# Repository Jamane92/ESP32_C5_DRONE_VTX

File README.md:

# ESP32_C5_DRONE_VTX

Ce projet à été réalisé individuellement en parallèle de mes études. C'est un module d'émission vidéo en digital à bas coût. Souhaitant me challenger dans mon parcours d'apprentissage en conception hardware, je me suis lancé le défi de construire un drone moi même, avec en première étape de ce gros projet, de faire un VTX ainsi qu'un Flight Controler (FC) de A à Z. Le projet Flight Controler est disponible sur cette page : https://github.com/Jamane92/Flight_Controler_STM32F405RGT6. 

Qu'est ce qu'un module VTX ? C'est un module d'émission vidéo, qui permet de transmettre la vue à la première personne du drone sur un écran au sol, que ce soit un téléphone ou un ordinateur par exemple. Cela permet de repérer le drone dans l'espace et de le faire voler à des endroits où nous ne pouvons pas voir. Un set complet bas/milieu de gamme coùute aux alentours de 200 à 250€. Ca fait mal. J'ai donc décidé, pour m'apprendre à implémenter une chip ESP32 sur PCB, de faire un PCB custom qui intègre une ESP32-C5-WROOM-1U-N8R8, une OV5640 ainsi qu'une carte SD, pour la somme ≈ 40€. Ce qui est un prix imbattable, tout simplement.

Le but de se projet est simple : d'un point de vue technique, m'apprendre à router des SoC (System On Chip) ainsi que des signaux critiques comme ceux de la caméra OV5640, le tout sur mon premier PCB 4 couches avec des composants SMD. Un grand pas donc depuis mon premier PCB sur mon robot équilibriste (https://github.com/Jamane92/Self_Balancing_Robot). Plus de détail dans les rubriques sur les choix de design (notamment sur des améliorations possibles).

Voilà à quoi ressemble le module : 

Plus en détail, le coeur au milieu, à gauche l'antenne Lollipop et à droite la caméra. Ce PCB à fonctionné du premier coup. Voici à quoi ressemble l'interface WEB : 

Voici un petit exemple de ce dont il est capable (entre autres : réglage de a qualité vidéo, compression, luminosité, saturation, contraste, filtre, enregistrement sur la SD Card) :

Voici une vidéo de mon balcon, au 3ème étage, avec l'exploration de tous les settings de la caméra : 

Voici une vidéo de moi en HVGA (480 × 320), gardez à l'esprit que l'on filmera en SVGA (800 × 600), soit littéralement 3 fois plus de pixels. 

Pour la démo en vol, il faudra attendre que le projet du flight controler (https://github.com/Jamane92/Flight_Controler_STM32F405RGT6) soit terminé. 

Pour voir les performances du montage, voir le folder dedié.

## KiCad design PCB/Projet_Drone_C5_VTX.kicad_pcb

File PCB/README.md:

Ce PCB contient **4 couches**, étant embarqué sur un drone, il possède des entrées d'alimentations **+5V**, que sont l'**USB-C**, également utilisé pour programmer l'**ESP32**, ainsi que des PADs de cuivre, qui viendront directement être branché à partir de mon flight controler. Il possède deux diodes Schottky pour faire du **OR'ing**. Une **OV5640**, un lecteur de **carte SD**, ainsi qu'un **module 1U** spécialement choisi pour la possibilité d'y brancher une **antenne**, qui est une **lollipop** en RHCP, mieux qu'une antenne "simple", car celle-ci émettra un signal en forme de cercle, parfaitement adapté pour une antenne en hauteur qui va communiquer avec le sol.

Je suis parti sur un **4 couches** pour me simplifier la vie. Mon stack-up est le suivant : 

  - L1 : SIGNAL
  - L2 : GND
  - L3 : GND
  - L4 : SIGNAL/POWER

Tous les composants sont sur la même face pour des raisons économiques (plus cher de faire les deux face lors de l'assemblage chez JLCPCB). 

Afin d'optimiser l'**intégrité des signaux**, de nombreux vias de masse (ground vias) ont été placés pour relier **(stitching)** les plans de masse entre les couches L2 et L3. Ce **stitching de masse assure un chemin de retour court**, direct et ininterrompu pour les signaux numériques à haute vitesse (bus de la caméra OV5640, interface de la carte SD) ainsi que pour la section RF à 5.8 GHz. Cela permet de **minimiser l'inductance des boucles de courant** et de **réduire drastiquement les interférences électromagnétiques** (EMI), un point absolument **critique** dans l'environnement très bruyant d'un drone (ESC, moteurs). 

L'**impédance** de la ligne de communication différentiel D+/D- est **matché à 90Ω**

Voici la schématique : 

Voici le routage : 

Voici la 3D :

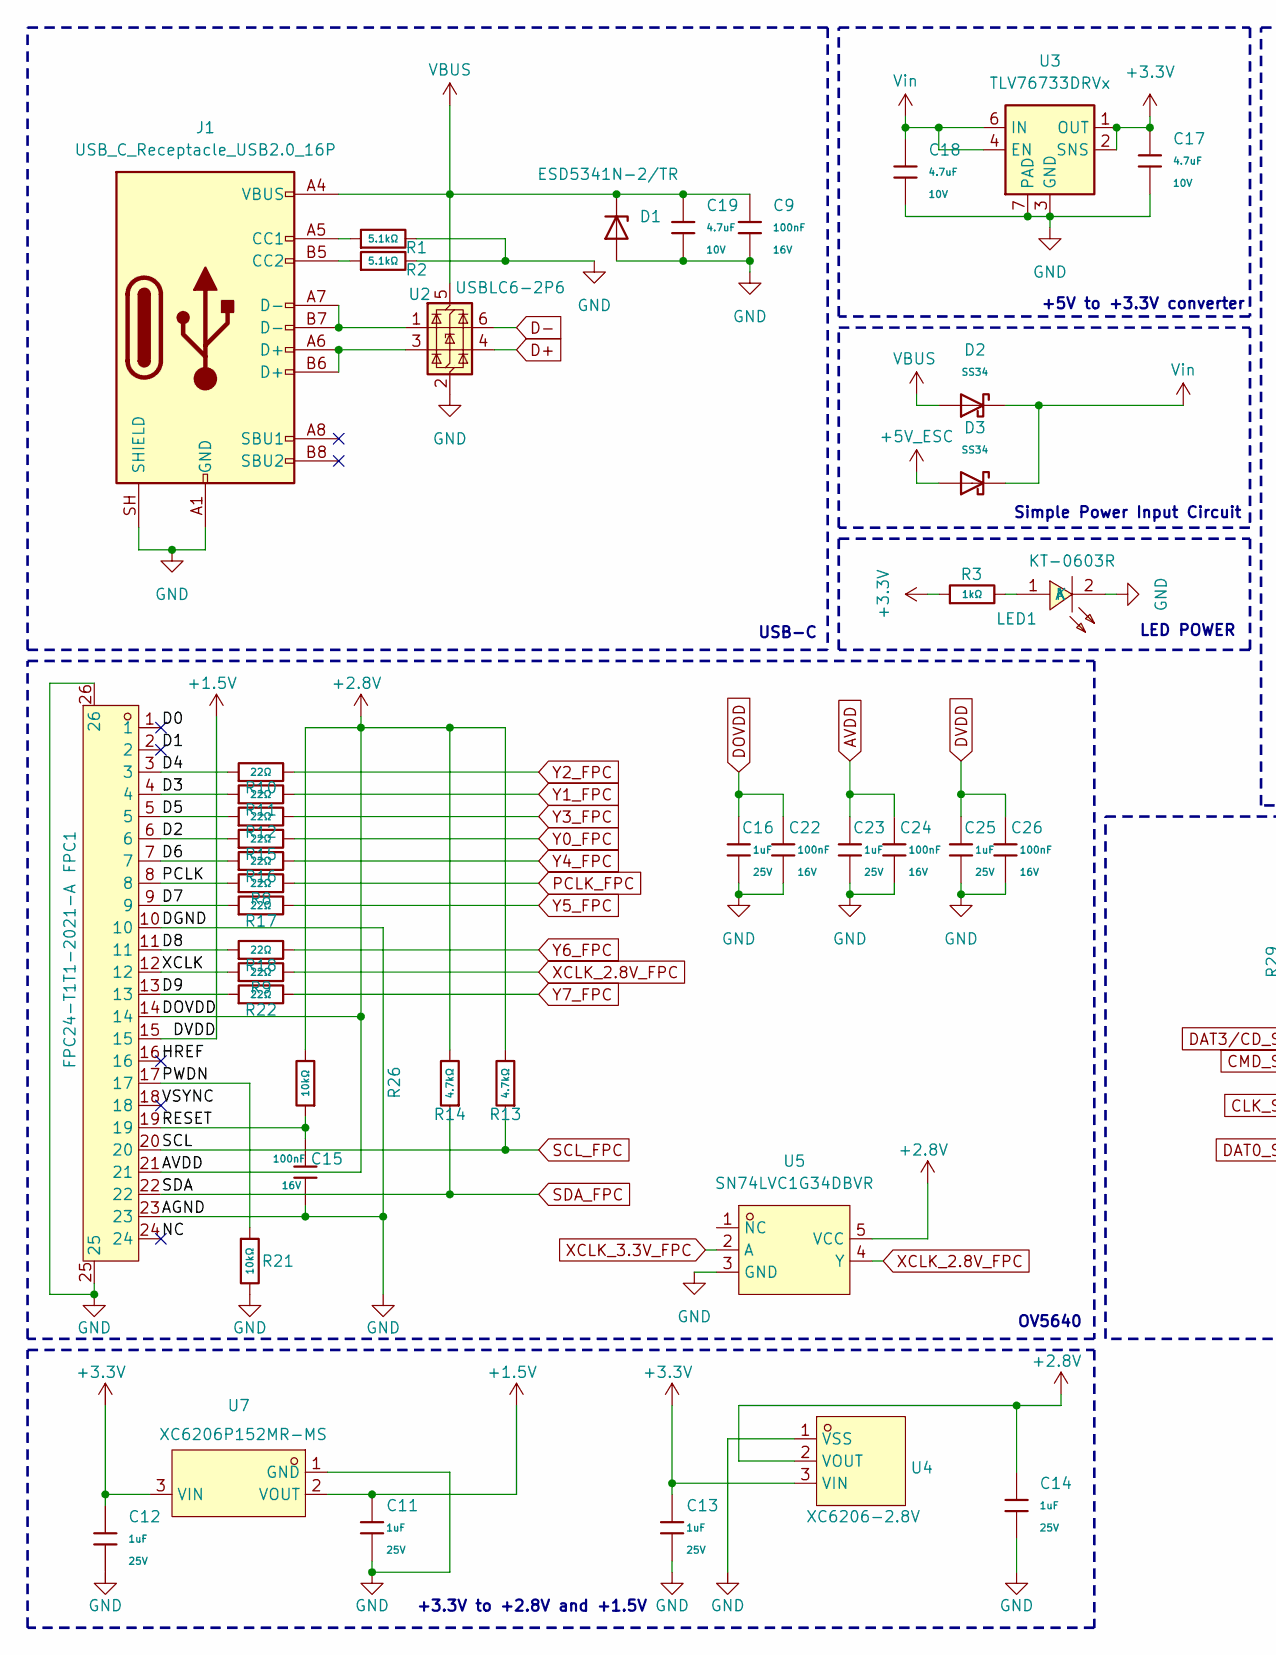
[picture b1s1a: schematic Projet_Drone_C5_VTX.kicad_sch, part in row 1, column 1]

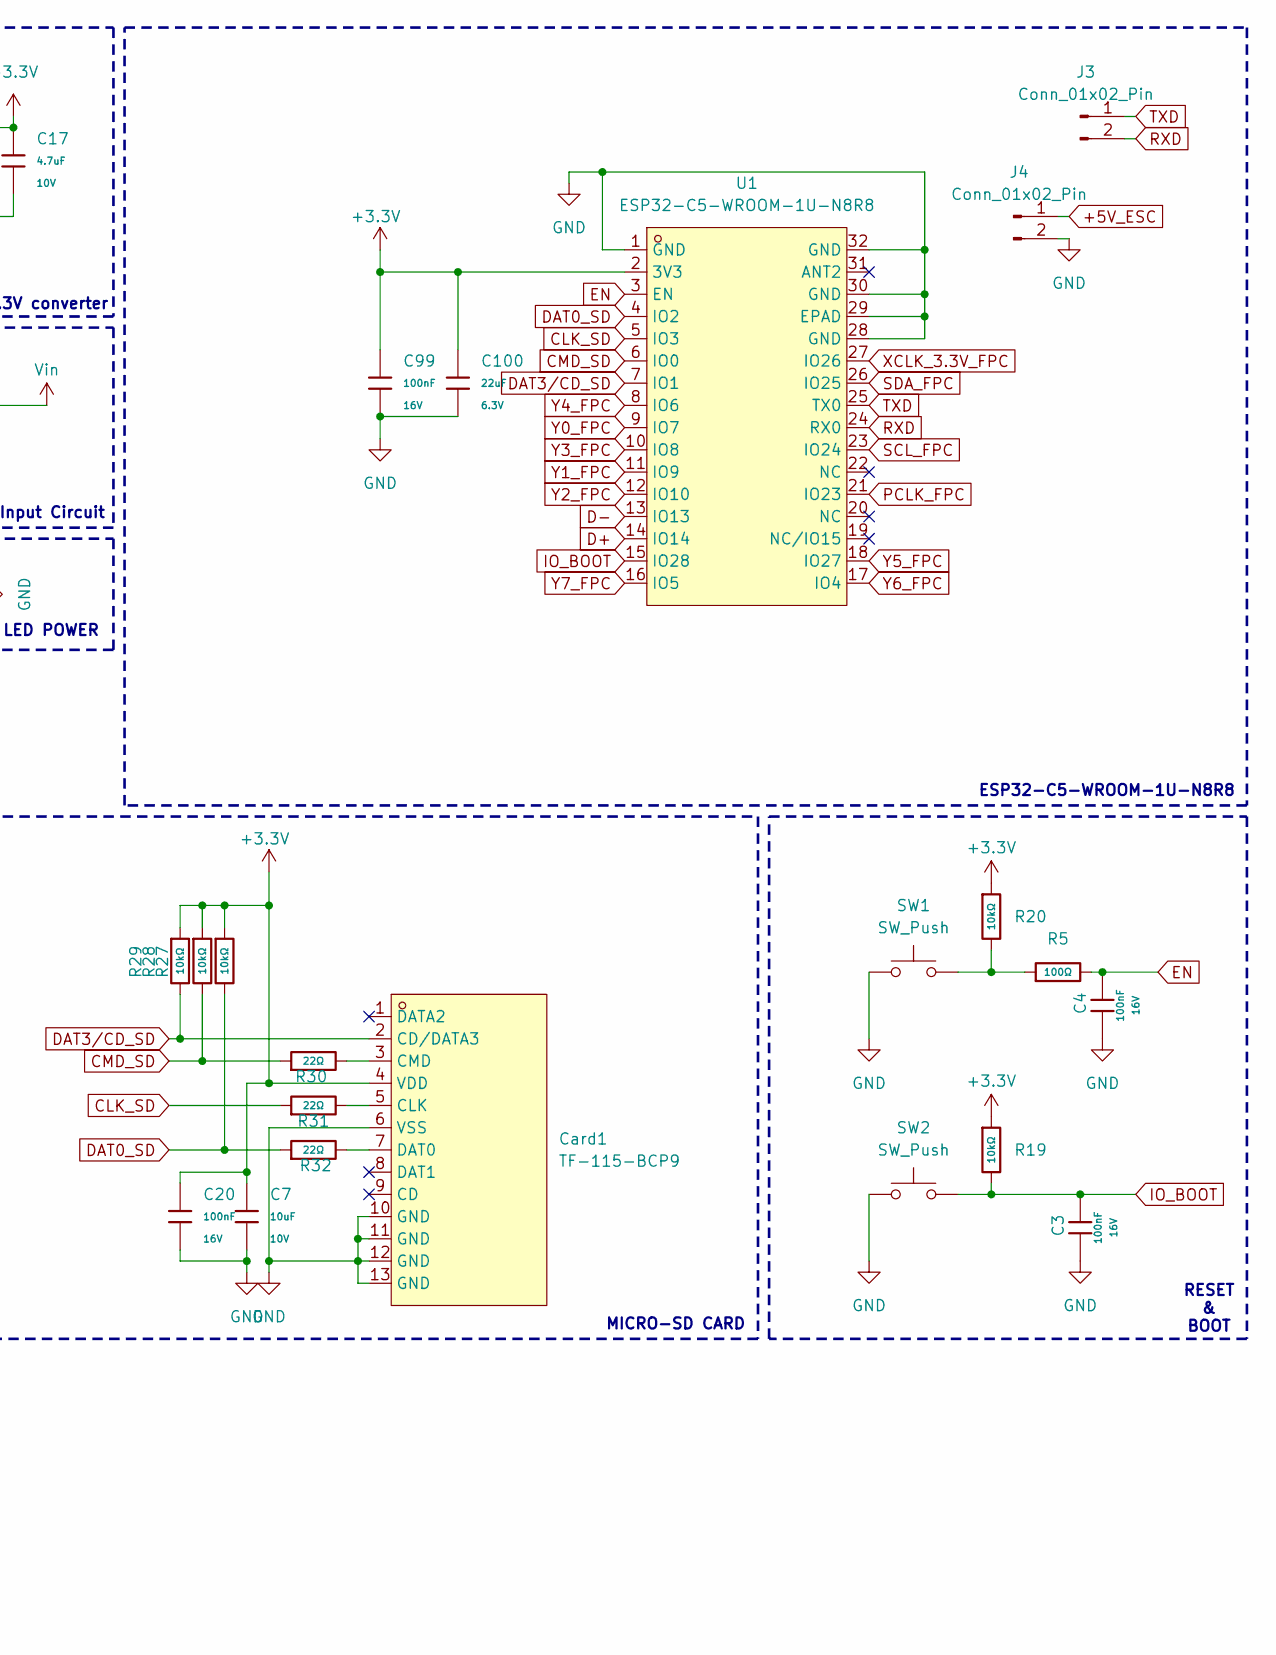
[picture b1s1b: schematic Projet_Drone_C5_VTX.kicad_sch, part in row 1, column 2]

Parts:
C3, C4, C9, C15, C20, C22, C24, C26, C99: 100nF; C_0402; Voltage Rated 16V; Tolerance ±10%; Part CL05B104KO5NNNC; LCSC C1525
C7: 10uF; C_0603; Voltage Rated 10V; Tolerance ±10%; Part CL10A106KP8NNNC; LCSC C19702
C11, C12, C13, C14, C16, C23, C25: 1uF; C_0402; Voltage Rated 25V; Tolerance ±10%; Part CL05A105KA5NQNC; LCSC C52923
C17, C18, C19: 4.7uF; C_0402; Voltage Rated 10V; Tolerance ±20%; Part CL05A475MP5NRNC; LCSC C23733
C100: 22uF; C_0603; Voltage Rated 6.3V; Tolerance ±20%; Part CL10A226MQ8NRNC; LCSC C59461
Card1: TF-115-BCP9; TF-SMD_TF-115-BCP9; MPN TF-115-BCP9; LCSC Part C720505
D1: ESD5341N-2/TR; DFN1006-2L-RD
D2, D3: SS34; D_SMA; Forward Voltage (Vf@If) 550mV@3A; Reverse Voltage (Vr) 40V; Part SS34; LCSC C8678
FPC1: FPC24-T1T1-2021-A; FPC-SMD_FPC24-T1T1-2021-A; MPN FPC24-T1T1-2021-A; LCSC Part C52740865
J1: USB_C_Receptacle_USB2.0_16P; USB_C_Receptacle_GCT_USB4105-xx-A_16P_TopMnt_Horizontal
J3, J4: Conn_01x02_Pin; SolderWire-0.127sqmm_1x02_P3.7mm_D0.48mm_OD1mm
LED1: KT-0603R; LED-SMD_L1.6-W0.8-R-RD; MPN KT-0603R; LCSC Part C2286
R1, R2: 5.1kΩ; R_0402; Overload Voltage (Max) 50V; Tolerance ±1%; Part 0402WGF5101TCE; LCSC C25905
R3: 1kΩ; R_0402; Overload Voltage (Max) 50V; Tolerance ±1%; Part 0402WGF1001TCE; LCSC C11702
R5: 100Ω; R_0805; Overload Voltage (Max) 150V; Tolerance ±1%; Part 0805W8F1000T5E; LCSC C17408
R8, R9, R10, R11, R12, R15, R16, R17, R18, R22, R30, R31, R32: 22Ω; R_0402; Overload Voltage (Max) 50V; Tolerance ±1%; Part 0402WGF220JTCE; LCSC C25092
R13, R14: 4.7kΩ; R_0402; Overload Voltage (Max) 50V; Tolerance ±1%; Part 0402WGF4701TCE; LCSC C25900
R19, R20, R21, R26, R27, R28, R29: 10kΩ; R_0603; Overload Voltage (Max) 75V; Tolerance ±1%; Part 0603WAF1002T5E; LCSC C25804
SW1, SW2: SW_Push; KEY-SMD_B3U-1000PM
U1: ESP32-C5-WROOM-1U-N8R8; COMM-SMD_32P-L21.2-W18.0_ESP32-C5-WROOM-1U; MPN ESP32-C5-WROOM-1U-N8R8; LCSC Part C51950748
U2: USBLC6-2P6; SOT-666
U3: TLV76733DRVx; WSON-6-1EP_2x2mm_P0.65mm_EP1x1.6mm_ThermalVias
U4: XC6206-2.8V; SOT-23-3_L2.9-W1.6-P1.90-LS2.8-BR; MPN XC6206-2.8V; LCSC Part C2892669
U5: SN74LVC1G34DBVR; SOT-23-5_L2.9-W1.6-P0.95-LS2.8-BR; MPN SN74LVC1G34DBVR; LCSC Part C840096
U7: XC6206P152MR-MS; SOT-23-3_L2.9-W1.3-P1.90-LS2.4-BR; MPN XC6206P152MR-MS; LCSC Part C30197512

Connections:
+3.3V: C7.1, C12.1, C13.1, C17.1, C20.1, C99.1, C100.1, Card1.4 (VDD), R3.1, R19.1, R20.1, R27.1, R28.1, R29.1, U1.2 (3V3), U3.1 (OUT), U3.2 (SNS), U4.3 (VIN), U7.3 (VIN)
+5V_ESC: D3.2, J4.1
/D0: FPC1.1
/D1: FPC1.2
/D2: FPC1.6, R15.1
/D3: FPC1.4, R11.1
/D4: FPC1.3, R10.1
/D5: FPC1.5, R12.1
/D6: FPC1.7, R16.1
/D7: FPC1.9, R17.1
/D8: FPC1.11, R18.1
/D9: FPC1.13, R22.1
/HREF: FPC1.16
/NC: FPC1.24
/PCLK: FPC1.8, R8.1
/PWDN: FPC1.17, R21.1
/RESET: C15.1, FPC1.19, R26.1
/VSYNC: FPC1.18
/XCLK: FPC1.12, R9.1
AVDD: C14.1, C16.1, C22.1, C23.1, C24.1, FPC1.14, FPC1.21, R13.2, R14.2, R26.2, U4.2 (VOUT), U5.5 (VCC)
CLK_SD: R31.1, U1.5 (IO3)
CMD_SD: R28.2, R30.1, U1.6 (IO0)
D+: U1.14 (IO14), U2.4 (I/O2)
D-: U1.13 (IO13), U2.6 (I/O1)
DAT0_SD: R29.2, R32.1, U1.4 (IO2)
DAT3/CD_SD: Card1.2 (CD/DATA3), R27.2, U1.7 (IO1)
DVDD: C11.1, C25.1, C26.1, FPC1.15, U7.2 (VOUT)
EN: C4.1, R5.2, U1.3 (EN)
GND: C3.2, C4.2, C7.2, C9.2, C11.2, C12.2, C13.2, C14.2, C15.2, C16.2, C17.2, C18.2, C19.2, C20.2, C22.2, C23.2, C24.2, C25.2, C26.2, C99.2, C100.2, Card1.6 (VSS), Card1.10 (GND), Card1.11 (GND), Card1.12 (GND), Card1.13 (GND), D1.2 (A), FPC1.10, FPC1.23, FPC1.25, FPC1.26, J1.A1 (GND), J1.A12 (GND), J1.B1 (GND), J1.B12 (GND), J1.SH (SHIELD), J4.2, LED1.2 (K), R1.2, R2.2, R21.2, SW1.1, SW2.1, U1.1 (GND), U1.28 (GND), U1.29 (EPAD), U1.30 (GND), U1.32 (GND), U2.2 (GND), U3.3 (GND), U3.5 (GND), U3.7 (PAD), U4.1 (VSS), U5.3 (GND), U7.1 (GND)
IO_BOOT: C3.1, R19.2, SW2.2, U1.15 (IO28)
unnamed: Card1.5 (CLK), R31.2
unnamed: Card1.3 (CMD), R30.2
unnamed: Card1.7 (DAT0), R32.2
unnamed: J1.A5 (CC1), R1.1
unnamed: J1.B5 (CC2), R2.1
unnamed: J1.A6 (D+), J1.B6 (D+), U2.3 (I/O2)
unnamed: J1.A7 (D-), J1.B7 (D-), U2.1 (I/O1)
unnamed: LED1.1 (A), R3.2
unnamed: R5.1, R20.2, SW1.2
PCLK_FPC: R8.2, U1.21 (IO23)
RXD: J3.2, U1.24 (RX0)
SCL_FPC: FPC1.20, R13.1, U1.23 (IO24)
SDA_FPC: FPC1.22, R14.1, U1.26 (IO25)
TXD: J3.1, U1.25 (TX0)
VBUS: C9.1, C19.1, D1.1 (K), D2.2, J1.A4 (VBUS), J1.A9 (VBUS), J1.B4 (VBUS), J1.B9 (VBUS), U2.5 (VBUS)
Vin: C18.1, D2.1, D3.1, U3.4 (EN), U3.6 (IN)
XCLK_2.8V_FPC: R9.2, U5.4 (Y)
XCLK_3.3V_FPC: U1.27 (IO26), U5.2 (A)
Y0_FPC: R15.2, U1.9 (IO7)
Y1_FPC: R11.2, U1.11 (IO9)
Y2_FPC: R10.2, U1.12 (IO10)
Y3_FPC: R12.2, U1.10 (IO8)
Y4_FPC: R16.2, U1.8 (IO6)
Y5_FPC: R17.2, U1.18 (IO27)
Y6_FPC: R18.2, U1.17 (IO4)
Y7_FPC: R22.2, U1.16 (IO5)

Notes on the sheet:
MICRO-SD CARD
+5V to +3.3V converter
LED POWER
+3.3V to +2.8V and +1.5V
USB-C
ESP32-C5-WROOM-1U-N8R8
RESET & BOOT
Simple Power Input Circuit
OV5640

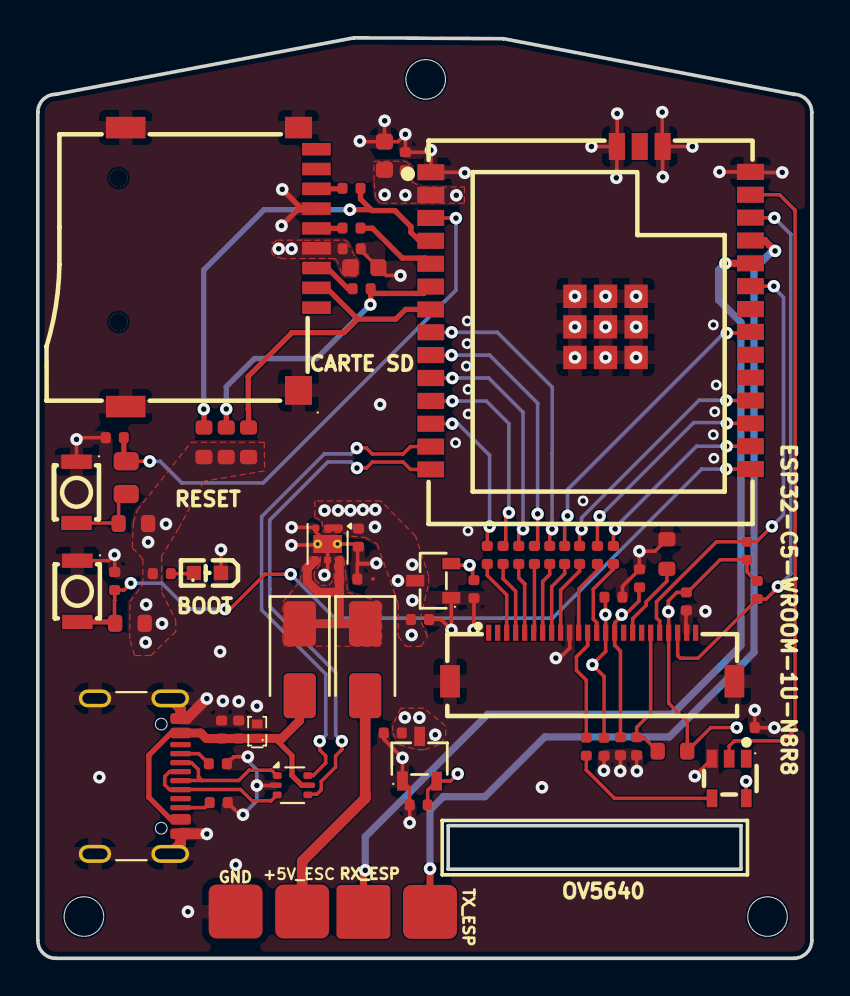
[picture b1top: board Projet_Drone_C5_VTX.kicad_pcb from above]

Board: 4 copper layers, 43.0 x 51.1 mm, 64 parts (0 on the bottom side), 51 nets.

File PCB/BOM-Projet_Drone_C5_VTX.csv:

Comment,Designator,Footprint,LCSC,Quantity
100nF,"C15,C20,C22,C24,C26,C3,C4,C9,C99",C_0402,C1525,9
100Ω,R5,R_0805,C17408,1
10kΩ,"R19,R20,R21,R26,R27,R28,R29",R_0603,C25804,7
10uF,C7,C_0603,C19702,1
1kΩ,R3,R_0402,C11702,1
1uF,"C11,C12,C13,C14,C16,C23,C25",C_0402,C52923,7
22uF,C100,C_0603,C59461,1
22Ω,"R10,R11,R12,R15,R16,R17,R18,R22,R30,R31,R32,R8,R9",R_0402,C25092,13
4.7kΩ,"R13,R14",R_0402,C25900,2
4.7uF,"C17,C18,C19",C_0402,C23733,3
5.1kΩ,"R1,R2",R_0402,C25905,2
ESD5341N-2/TR,D1,DFN1006-2L-RD,C239773,1
ESP32-C5-WROOM-1U-N8R8,U1,COMM-SMD_32P-L21.2-W18.0_ESP32-C5-WROOM-1U,C51950748,1
FPC24-T1T1-2021-A,FPC1,FPC-SMD_FPC24-T1T1-2021-A,C52740865,1
KT-0603R,LED1,LED-SMD_L1.6-W0.8-R-RD,C2286,1
SN74LVC1G34DBVR,U5,SOT-23-5_L2.9-W1.6-P0.95-LS2.8-BR,C840096,1
SS34,"D2,D3",D_SMA,C8678,2
SW_Push,"SW1,SW2",KEY-SMD_B3U-1000PM,C231329,2
TF-115-BCP9,Card1,TF-SMD_TF-115-BCP9,C720505,1
TLV76733DRVx,U3,WSON-6-1EP_2x2mm_P0.65mm_EP1x1.6mm_ThermalVias,C2848334,1
USBLC6-2P6,U2,SOT-666,C22390016,1
USB_C_Receptacle_USB2.0_16P,J1,USB_C_Receptacle_GCT_USB4105-xx-A_16P_TopMnt_Horizontal,C5184243,1
XC6206-2.8V,U4,SOT-23-3_L2.9-W1.6-P1.90-LS2.8-BR,C2892669,1
XC6206P152MR-MS,U7,SOT-23-3_L2.9-W1.3-P1.90-LS2.4-BR,C30197512,1
Conn_01x02_Pin,J4,SolderWire-0.127sqmm_1x02_P3.7mm_D0.48mm_OD1mm,,1
Conn_01x02_Pin,J3,SolderWire-0.127sqmm_1x02_P3.7mm_D0.48mm_OD1mm,,1
